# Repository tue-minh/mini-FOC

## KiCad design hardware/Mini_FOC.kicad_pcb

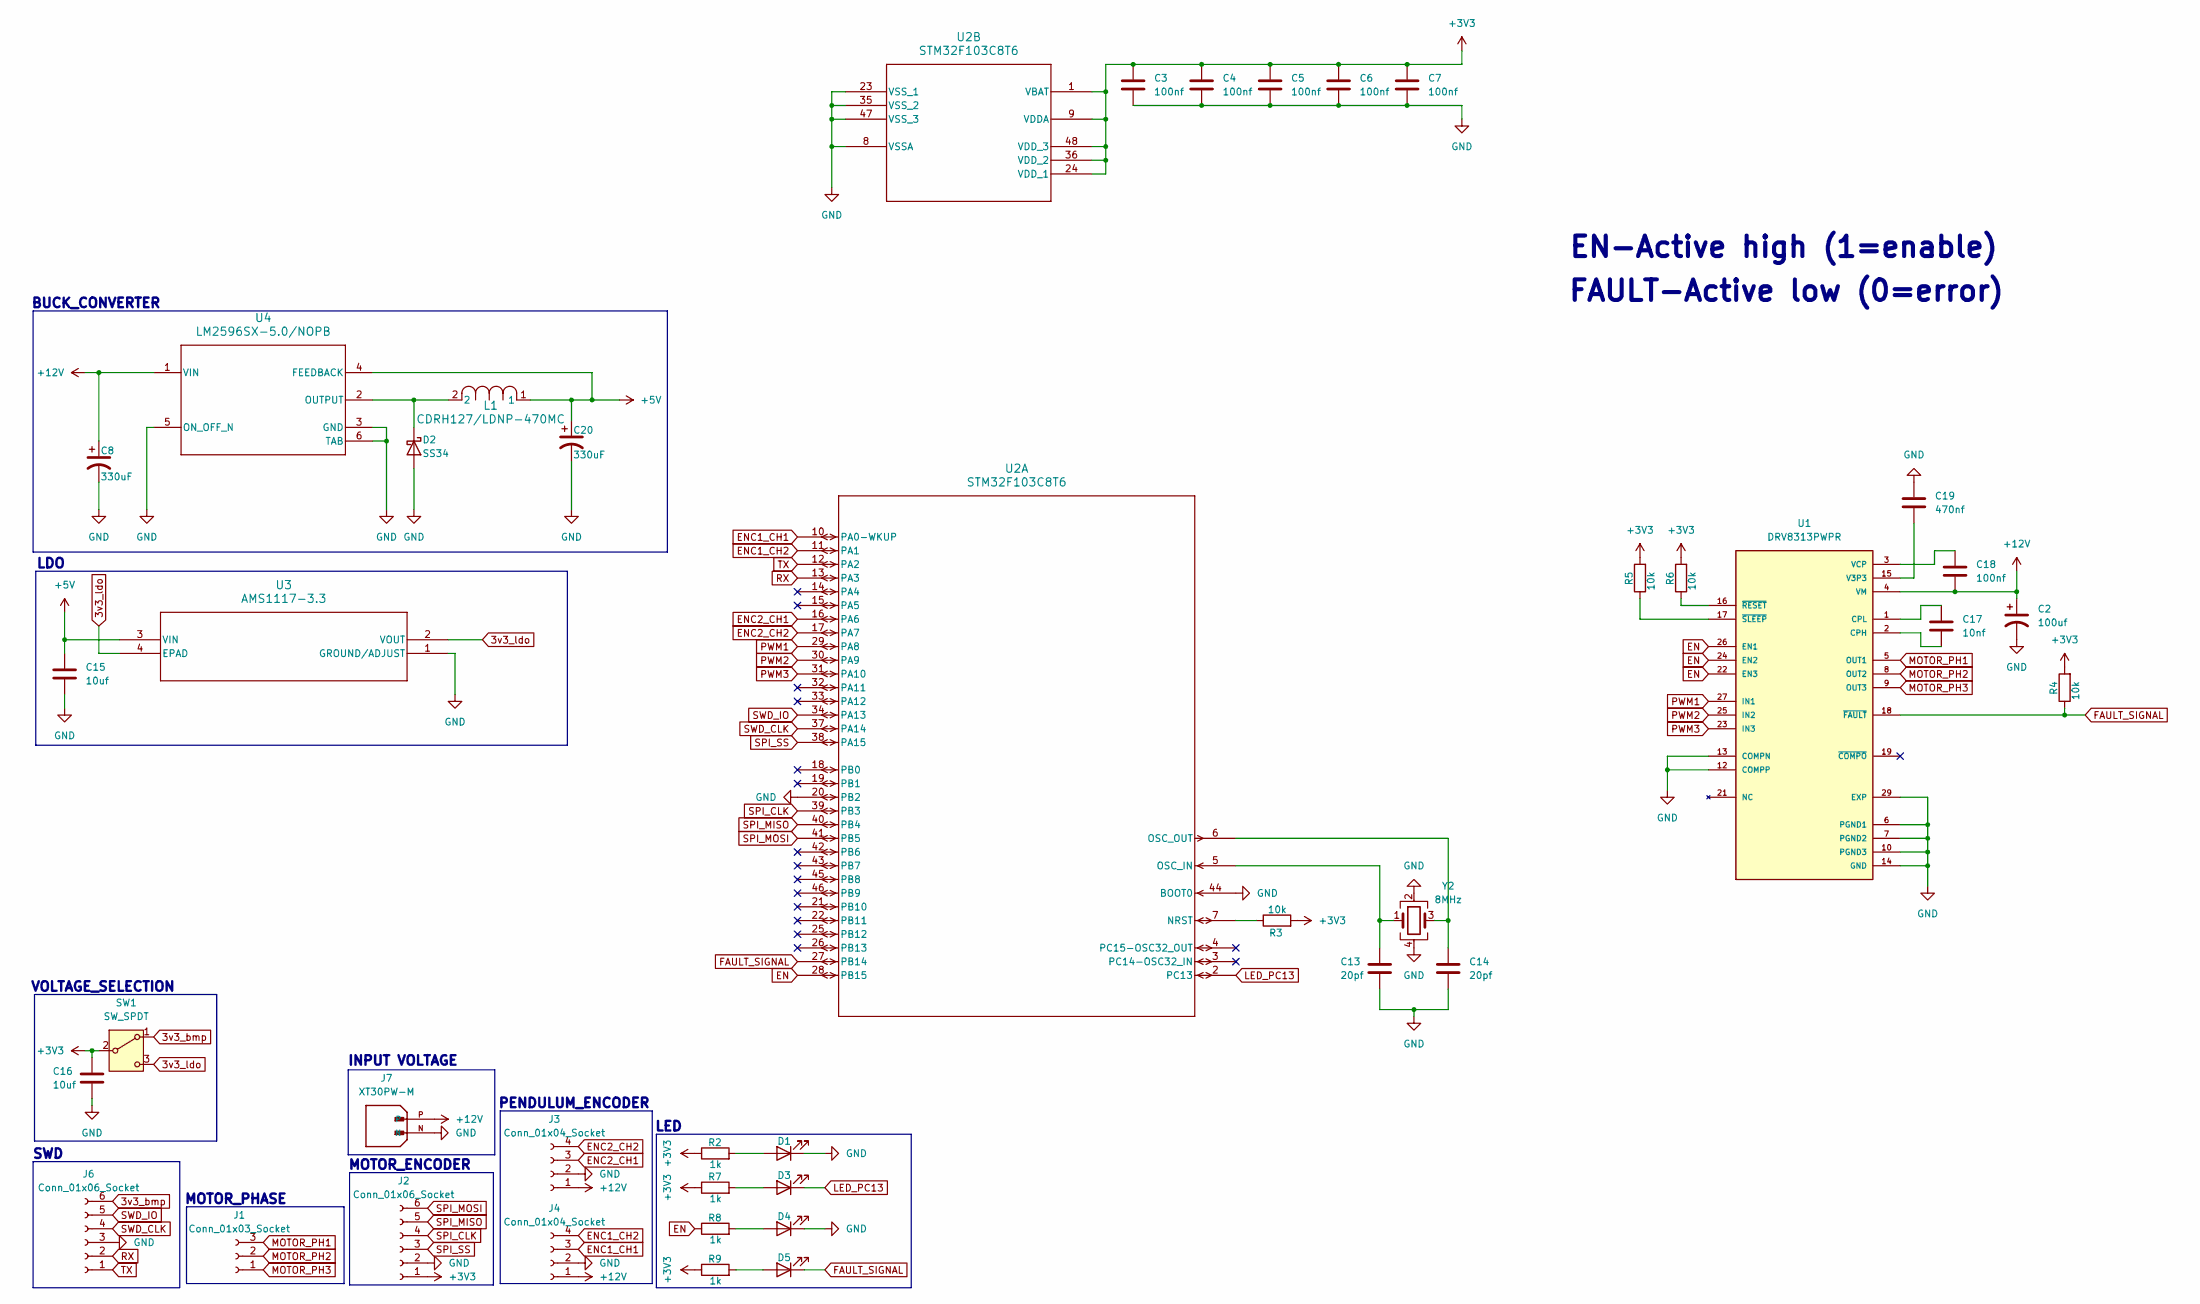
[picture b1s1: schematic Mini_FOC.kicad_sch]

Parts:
C2: 100uf; CP_Radial_D10.0mm_P5.00mm
C3, C4, C5, C6, C7, C18: 100nf; C_0603_1608Metric_Pad1.08x0.95mm_HandSolder
C8, C20: 330uF; CP_Radial_D10.0mm_P5.00mm
C13, C14: 20pf; C_0603_1608Metric_Pad1.08x0.95mm_HandSolder
C15, C16: 10uf; C_0603_1608Metric_Pad1.08x0.95mm_HandSolder
C17: 10nf; C_0603_1608Metric_Pad1.08x0.95mm_HandSolder
C19: 470nf; C_0603_1608Metric_Pad1.08x0.95mm_HandSolder
D1, D3, D4, D5: LED; LED_0603_1608Metric_Pad1.05x0.95mm_HandSolder
D2: SS34; D_SMA
J1: Conn_01x03_Socket; TerminalBlock_bornier-3_P5.08mm
J2: Conn_01x06_Socket; JST_ZH_B6B-ZR_1x06_P1.50mm_Vertical
J3, J4: Conn_01x04_Socket; JST_ZH_B4B-ZR_1x04_P1.50mm_Vertical
J6: Conn_01x06_Socket; JST_XH_B6B-XH-A_1x06_P2.50mm_Vertical
J7: XT30PW-M; AMASS_XT30PW-M; PARTREV 1.2
L1: CDRH127/LDNP-470MC; tue__CDRH127LDNP-470MC_SUM
R2, R7, R8, R9: 1k; R_0603_1608Metric_Pad0.98x0.95mm_HandSolder
R3, R4, R5, R6: 10k; R_0603_1608Metric_Pad0.98x0.95mm_HandSolder
SW1: SW_SPDT; tue_SS12D00_3P_2.5mm
U1: DRV8313PWPR; SOP65P640X120-29N; PARTREV D
U2: STM32F103C8T6; LQFP48_STM
U3: AMS1117-3.3; SOT_AMS_ADS
U4: LM2596SX-5.0/NOPB; tue_lm2596
Y2: 8MHz; Crystal_SMD_5032-4Pin_5.0x3.2mm

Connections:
3v3_bmp: J6.6, SW1.1 (A)
3v3_ldo: SW1.3 (C), U3.2 (VOUT), U3.4 (EPAD)
+3V3: C3.1, C4.1, C5.1, C6.1, C7.1, C16.1, J2.1, R2.1, R3.2, R4.2, R5.2, R6.2, R7.1, R9.1, SW1.2 (B), U2.1 (VBAT), U2.9 (VDDA), U2.24 (VDD_1), U2.36 (VDD_2), U2.48 (VDD_3)
+5V: C15.1, C20.1, L1.1, U3.3 (VIN), U4.4 (FEEDBACK)
+12V: C2.1, C8.1, C18.2, J3.1, J4.1, J7.P, U1.4 (VM), U1.11 (VM), U4.1 (VIN)
EN: R8.1, U1.22 (EN3), U1.24 (EN2), U1.26 (EN1), U2.28 (PB15)
ENC1_CH1: J4.3, U2.10 (PA0-WKUP)
ENC1_CH2: J4.4, U2.11 (PA1)
ENC2_CH1: J3.3, U2.16 (PA6)
ENC2_CH2: J3.4, U2.17 (PA7)
FAULT_SIGNAL: D5.1 (K), R4.1, U1.18 (~FAULT), U2.27 (PB14)
GND: C2.2, C3.2, C4.2, C5.2, C6.2, C7.2, C8.2, C13.2, C14.2, C15.2, C16.2, C19.1, C20.2, D1.1 (K), D2.2 (A), D4.1 (K), J2.2, J3.2, J4.2, J6.3, J7.N, U1.6 (PGND1), U1.7 (PGND2), U1.10 (PGND3), U1.12 (COMPP), U1.13 (COMPN), U1.14 (GND), U1.20 (GND), U1.28 (GND), U1.29 (EXP), U2.8 (VSSA), U2.20 (PB2), U2.23 (VSS_1), U2.35 (VSS_2), U2.44 (BOOT0), U2.47 (VSS_3), U3.1 (GROUND/ADJUST), U4.3 (GND), U4.5 (ON_OFF_N), U4.6 (TAB), Y2.2, Y2.4
LED_PC13: D3.1 (K), U2.2 (PC13)
MOTOR_PH1: J1.3, U1.5 (OUT1)
MOTOR_PH2: J1.2, U1.8 (OUT2)
MOTOR_PH3: J1.1, U1.9 (OUT3)
unnamed: D1.2 (A), R2.2
unnamed: D2.1 (K), L1.2, U4.2 (OUTPUT)
unnamed: D3.2 (A), R7.2
unnamed: D4.2 (A), R8.2
unnamed: D5.2 (A), R9.2
unnamed: C17.2, U1.2 (CPH)
unnamed: C17.1, U1.1 (CPL)
unnamed: C19.2, U1.15 (V3P3)
unnamed: C18.1, U1.3 (VCP)
unnamed: R6.1, U1.16 (~RESET)
unnamed: R5.1, U1.17 (~SLEEP)
unnamed: R3.1, U2.7 (NRST)
unnamed: C13.1, U2.5 (OSC_IN), Y2.1
unnamed: C14.1, U2.6 (OSC_OUT), Y2.3
PWM1: U1.27 (IN1), U2.29 (PA8)
PWM2: U1.25 (IN2), U2.30 (PA9)
PWM3: U1.23 (IN3), U2.31 (PA10)
RX: J6.2, U2.13 (PA3)
SPI_CLK: J2.4, U2.39 (PB3)
SPI_MISO: J2.5, U2.40 (PB4)
SPI_MOSI: J2.6, U2.41 (PB5)
SPI_SS: J2.3, U2.38 (PA15)
SWD_CLK: J6.4, U2.37 (PA14)
SWD_IO: J6.5, U2.34 (PA13)
TX: J6.1, U2.12 (PA2)

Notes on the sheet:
MOTOR_PHASE
VOLTAGE_SELECTION
LDO
INPUT VOLTAGE
BUCK_CONVERTER
PENDULUM_ENCODER
MOTOR_ENCODER
LED
EN-Active high (1=enable)
FAULT-Active low (0=error)
SWD

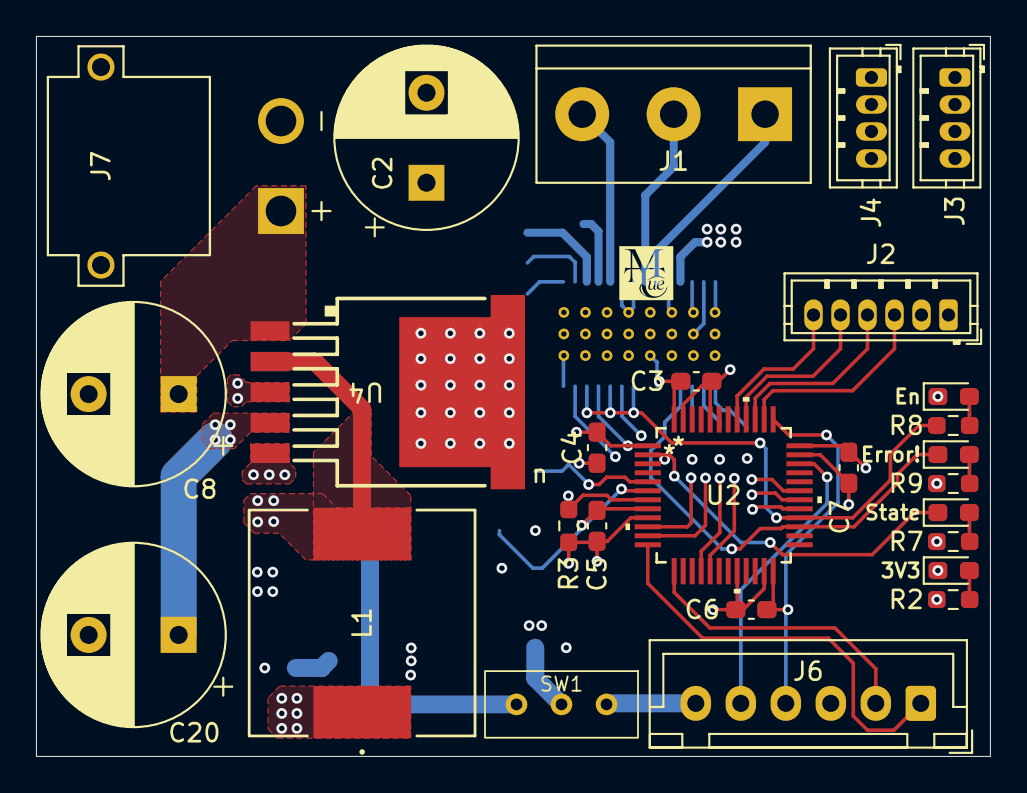
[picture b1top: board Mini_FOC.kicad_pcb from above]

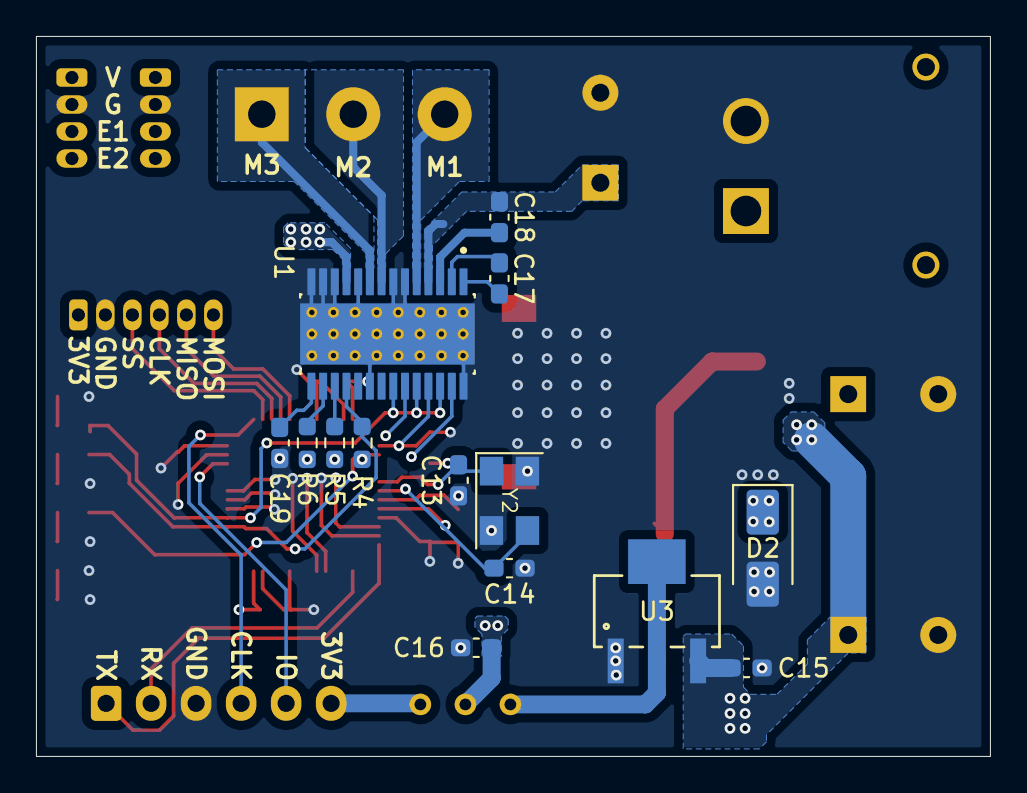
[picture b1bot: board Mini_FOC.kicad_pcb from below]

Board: 4 copper layers, 53.0 x 40.0 mm, 41 parts (14 on the bottom side), 41 nets.

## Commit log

2026-05-06 add hardware circuit
2026-05-07 minimize the pcb & add logo
2026-05-07 replace power connector
